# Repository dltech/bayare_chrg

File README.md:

# bayare_chrg
lazy variant of automatic car battery charger, based on transformer and 8-bit MCU

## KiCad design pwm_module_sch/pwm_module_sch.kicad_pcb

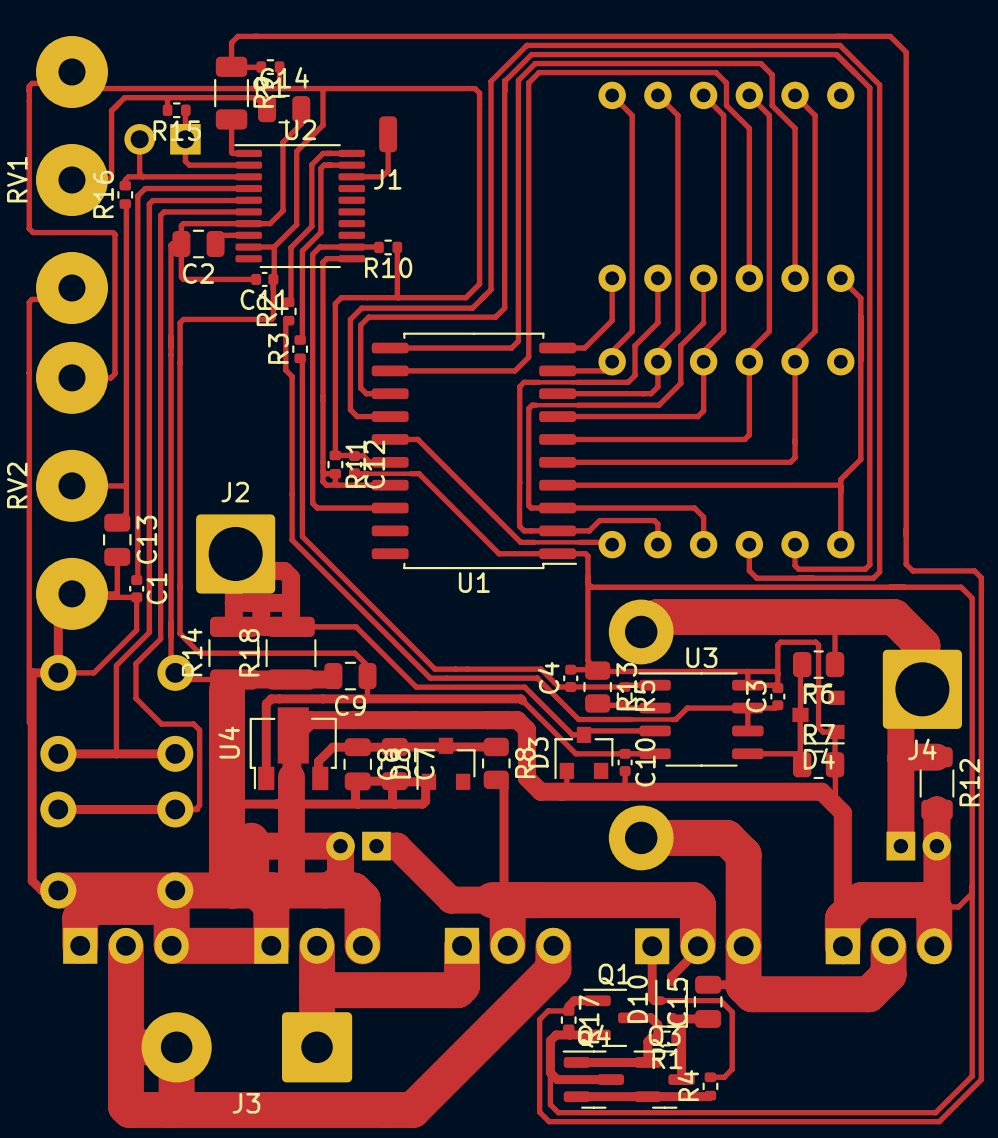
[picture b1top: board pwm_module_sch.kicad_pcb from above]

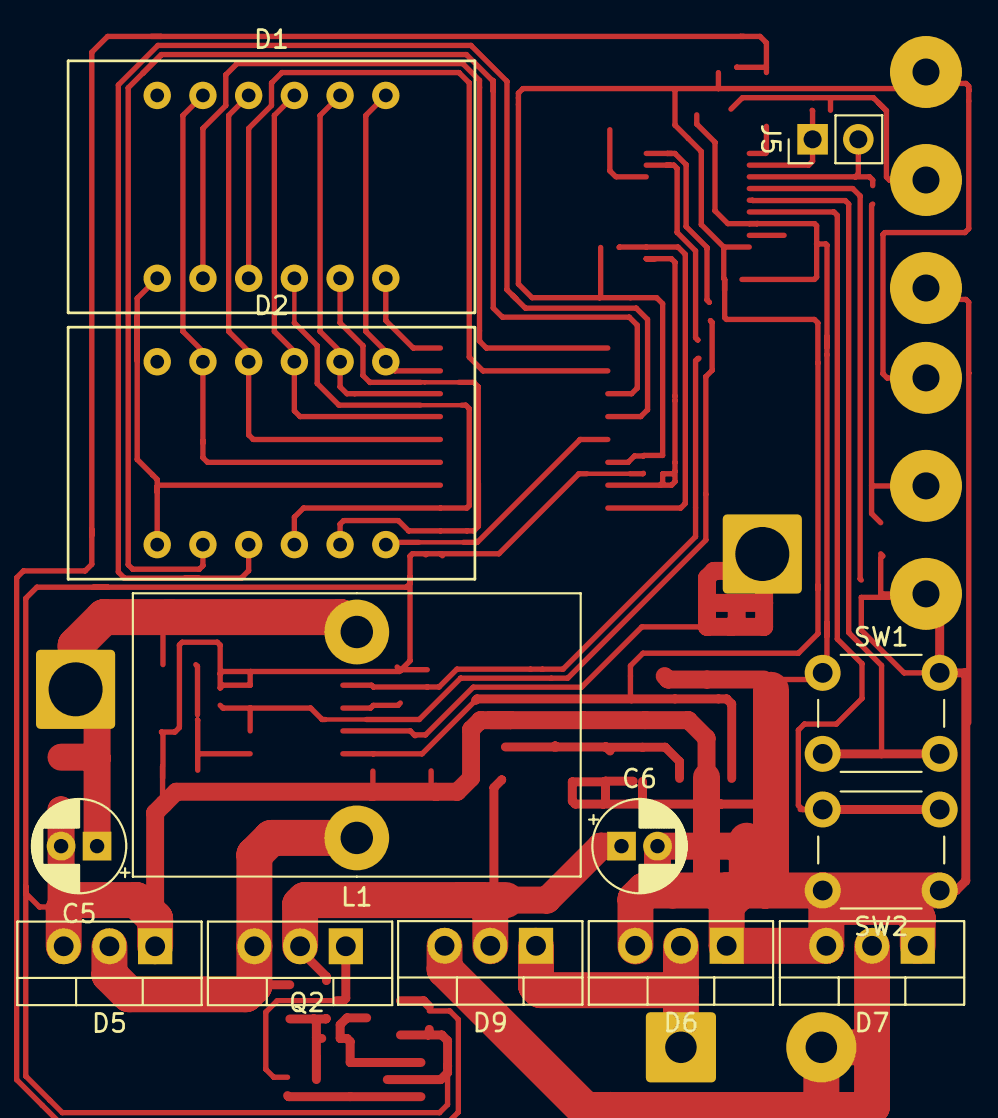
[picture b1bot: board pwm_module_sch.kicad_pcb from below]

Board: 2 copper layers, 62 parts (13 on the bottom side), 46 nets.

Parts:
C1, C3, C4, C10, C11, C12: 0.1uF; C_0402_1005Metric
C2, C13, C14: 1uF; C_0805_2012Metric
C5, C6: 1000uF; CP_Radial_D5.0mm_P2.00mm
C7, C9, C15: 10uF; C_0805_2012Metric
C8: 0.1uF; C_0805_2012Metric
D1, D2: LED_3digit; FYT-3631
D3, D4: BZX84C5V6; D_SOT-23_ANK
D5, D6, D7, D9: .; TO-220-3_Vertical
D8: PESD1CAN; D_SOT-23_ANK
D10: 1N5822; D_SOD-323
J1: SWIMM; SolderWirePad_1x01_SMD_1x2mm
J2: output -; SolderWire-2.5sqmm_1x01_D2.4mm_OD4.4mm
J3: input; SolderWire-1sqmm_1x02_P7.8mm_D1.4mm_OD3.9mm
J4: output+; SolderWire-2.5sqmm_1x01_D2.4mm_OD4.4mm
J5: uart; PinHeader_1x02_P2.54mm_Vertical
L1: 100uH; L_Toroid_Vertical_L24.6mm_W15.5mm_P11.44mm_Pulse_KM-4
Q1: AO3400; SOT-23
Q2: IRFZ44N; TO-220-3_Vertical
Q3: MMBTA42; SOT-23
Q4: MMBTA92; SOT-23
R1, R1#2, R5, R10, R11: 100k; R_0402_1005Metric
R2, R3, R15, R16: 75; R_0402_1005Metric
R4, R17: 1k; R_0402_1005Metric
R6: 100k; R_0805_2012Metric
R7: 10k; R_0805_2012Metric
R8: 10R; R_0805_2012Metric
R9: 75; R_1206_3216Metric
R12: 10k; R_1206_3216Metric
R13: 5.1k; R_0805_2012Metric
R14, R18: 0.01R; R_1210_3225Metric
RV1, RV2: .; SP3-4
SW1, SW2: .; SW_PUSH_6mm
U1: TM1637; SOIC-20W_7.5x12.8mm_P1.27mm
U2: STM8S003F3P; TSSOP-20_4.4x6.5mm_P0.65mm
U3: LM358; SO-8_3.9x4.9mm_P1.27mm
U4: L78L33; SOT-89-3

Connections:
+3V3: C9.1, C10.1, C11.1, C12.1, R1.1, R10.1, R11.1, RV1.3, RV2.3, U1.16 (VDD), U2.9 (VDD), U3.4 (V-), U4.1 (OUT)
+24V: C6.1, D9.2 (A), D10.2 (A), Q2.2 (D), R8.2
+VSW: C5.1, L1.2, R6.1, R12.2
-VSW: J2.1, R14.2, R18.2, U3.3 (+)
GND: C1.2, C2.2, C3.2, C4.2, C5.2, C6.2, C7.2, C8.2, C9.2, C10.2, C11.2, C12.2, C13.2, C14.2, D3.1 (A), D4.1 (A), D5.1 (K), D5.3 (K), D6.1 (K), D6.3 (K), D7.1 (K), D7.3 (K), D8.1 (A), Q1.2 (S), Q4.3 (C), R7.2, R12.1, R13.1, R14.1, R17.2, R18.1, RV1.1, RV2.1, SW1.1, SW2.1, U1.1 (GND), U2.7 (VSS), U3.8 (V+), U4.2 (GND)
unnamed: C1.1, U2.4 (NRST)
unnamed: C2.1, U2.8 (VCAP)
unnamed: C3.1, R2.1, U3.6 (-), U3.7
unnamed: C4.1, R3.1, R5.1, U3.1
unnamed: C7.1, C8.1, R8.1, U4.3 (IN)
unnamed: C13.1, R16.1, RV2.2
unnamed: C14.1, R15.2, RV1.2
unnamed: C15.1, D10.1 (K), Q3.3 (C), R1#2.1
unnamed: D1.1 (E), D2.1 (E), U1.9 (SEG8)
unnamed: D1.2 (D), D2.2 (D), U1.8 (SEG7)
unnamed: D1.3 (DP), D2.3 (DP), U1.7 (SEG6)
unnamed: D1.4 (C), D2.4 (C), U1.6 (SEG5)
unnamed: D1.5 (G), D2.5 (G), U1.5 (SEG4)
unnamed: D1.7 (B), D2.7 (B), U1.4 (SEG3)
unnamed: D1.8 (CA_DIG3), U1.11 (GRID5)
unnamed: D1.9 (CA_DIG2), U1.12 (GRID4)
unnamed: D1.10 (F), D2.10 (F), U1.3 (SEG2)
unnamed: D1.11 (A), D2.11 (A), U1.2 (SEG1)
unnamed: D1.12 (CA_DIG1), U1.10 (GRID6)
unnamed: D2.8 (CA_DIG3), U1.13 (GRID3)
unnamed: D2.9 (CA_DIG2), U1.14 (GRID2)
unnamed: D2.12 (CA_DIG1), U1.15 (GRID1)
unnamed: R6.2, R7.1, U3.5 (+)
unnamed: D6.2 (A), D9.1 (K), J3.1
unnamed: D7.2 (A), D9.3 (K), J3.2
unnamed: J1.1, U2.18 (PD1)
unnamed: J5.1, R15.1, U2.2 (PD5)
unnamed: J5.2, R16.2, U2.3 (PD6)
unnamed: Q1.1 (G), R1.2, R9.1, R17.1
unnamed: Q2.1 (G), R4.2
unnamed: C15.2, D5.2 (A), L1.1, Q2.3 (S)
unnamed: Q1.3 (D), Q3.1 (B), Q4.1 (B), R1#2.2
unnamed: Q3.2 (E), Q4.2 (E), R4.1
unnamed: R2.2, U2.20 (PD3)
unnamed: R3.2, U2.19 (PD2)
unnamed: R10.2, U1.18 (CLK), U2.12 (PB4)
unnamed: R11.2, U1.17 (DIO), U2.11 (PB5)
unnamed: R5.2, R13.2, U3.2 (-)
unnamed: SW1.2, U2.5 (PA1)
unnamed: SW2.2, U2.6 (PA2)
unnamed: R9.2, U2.1 (PD4)

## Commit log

2022-02-08 registers and make
2022-02-08 interrupt priority level and gpio regs.
2022-02-08 tim1 regs, gpio functions
2022-02-09 adc, clt, timer registers
2022-02-09 ignore
2022-02-09 schermatic
2022-02-10 clock on func, pcb assignment
2022-02-11 one-layer PCB 6x6cm
2022-02-15 tm adapt, pwm add
2022-02-17 init adc
2022-02-19 low lewel written, not tested, todo: main menu
2022-02-20 auto charge 8-bit adapted, todo:test
2022-02-20 compiled, not tested
2022-02-24 uart sch add
2022-02-27 reduced dimentions
2022-03-03 0402 caps
2022-03-03 10A shunt
2022-03-06 board ok
2022-03-17 working UART on board
2022-03-22 transistor
2022-03-23 inductor
2022-03-24 board fixed
2022-07-15 mosfet driver added
